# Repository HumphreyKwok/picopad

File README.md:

# picopad
A Cherry-mx numpad for fun

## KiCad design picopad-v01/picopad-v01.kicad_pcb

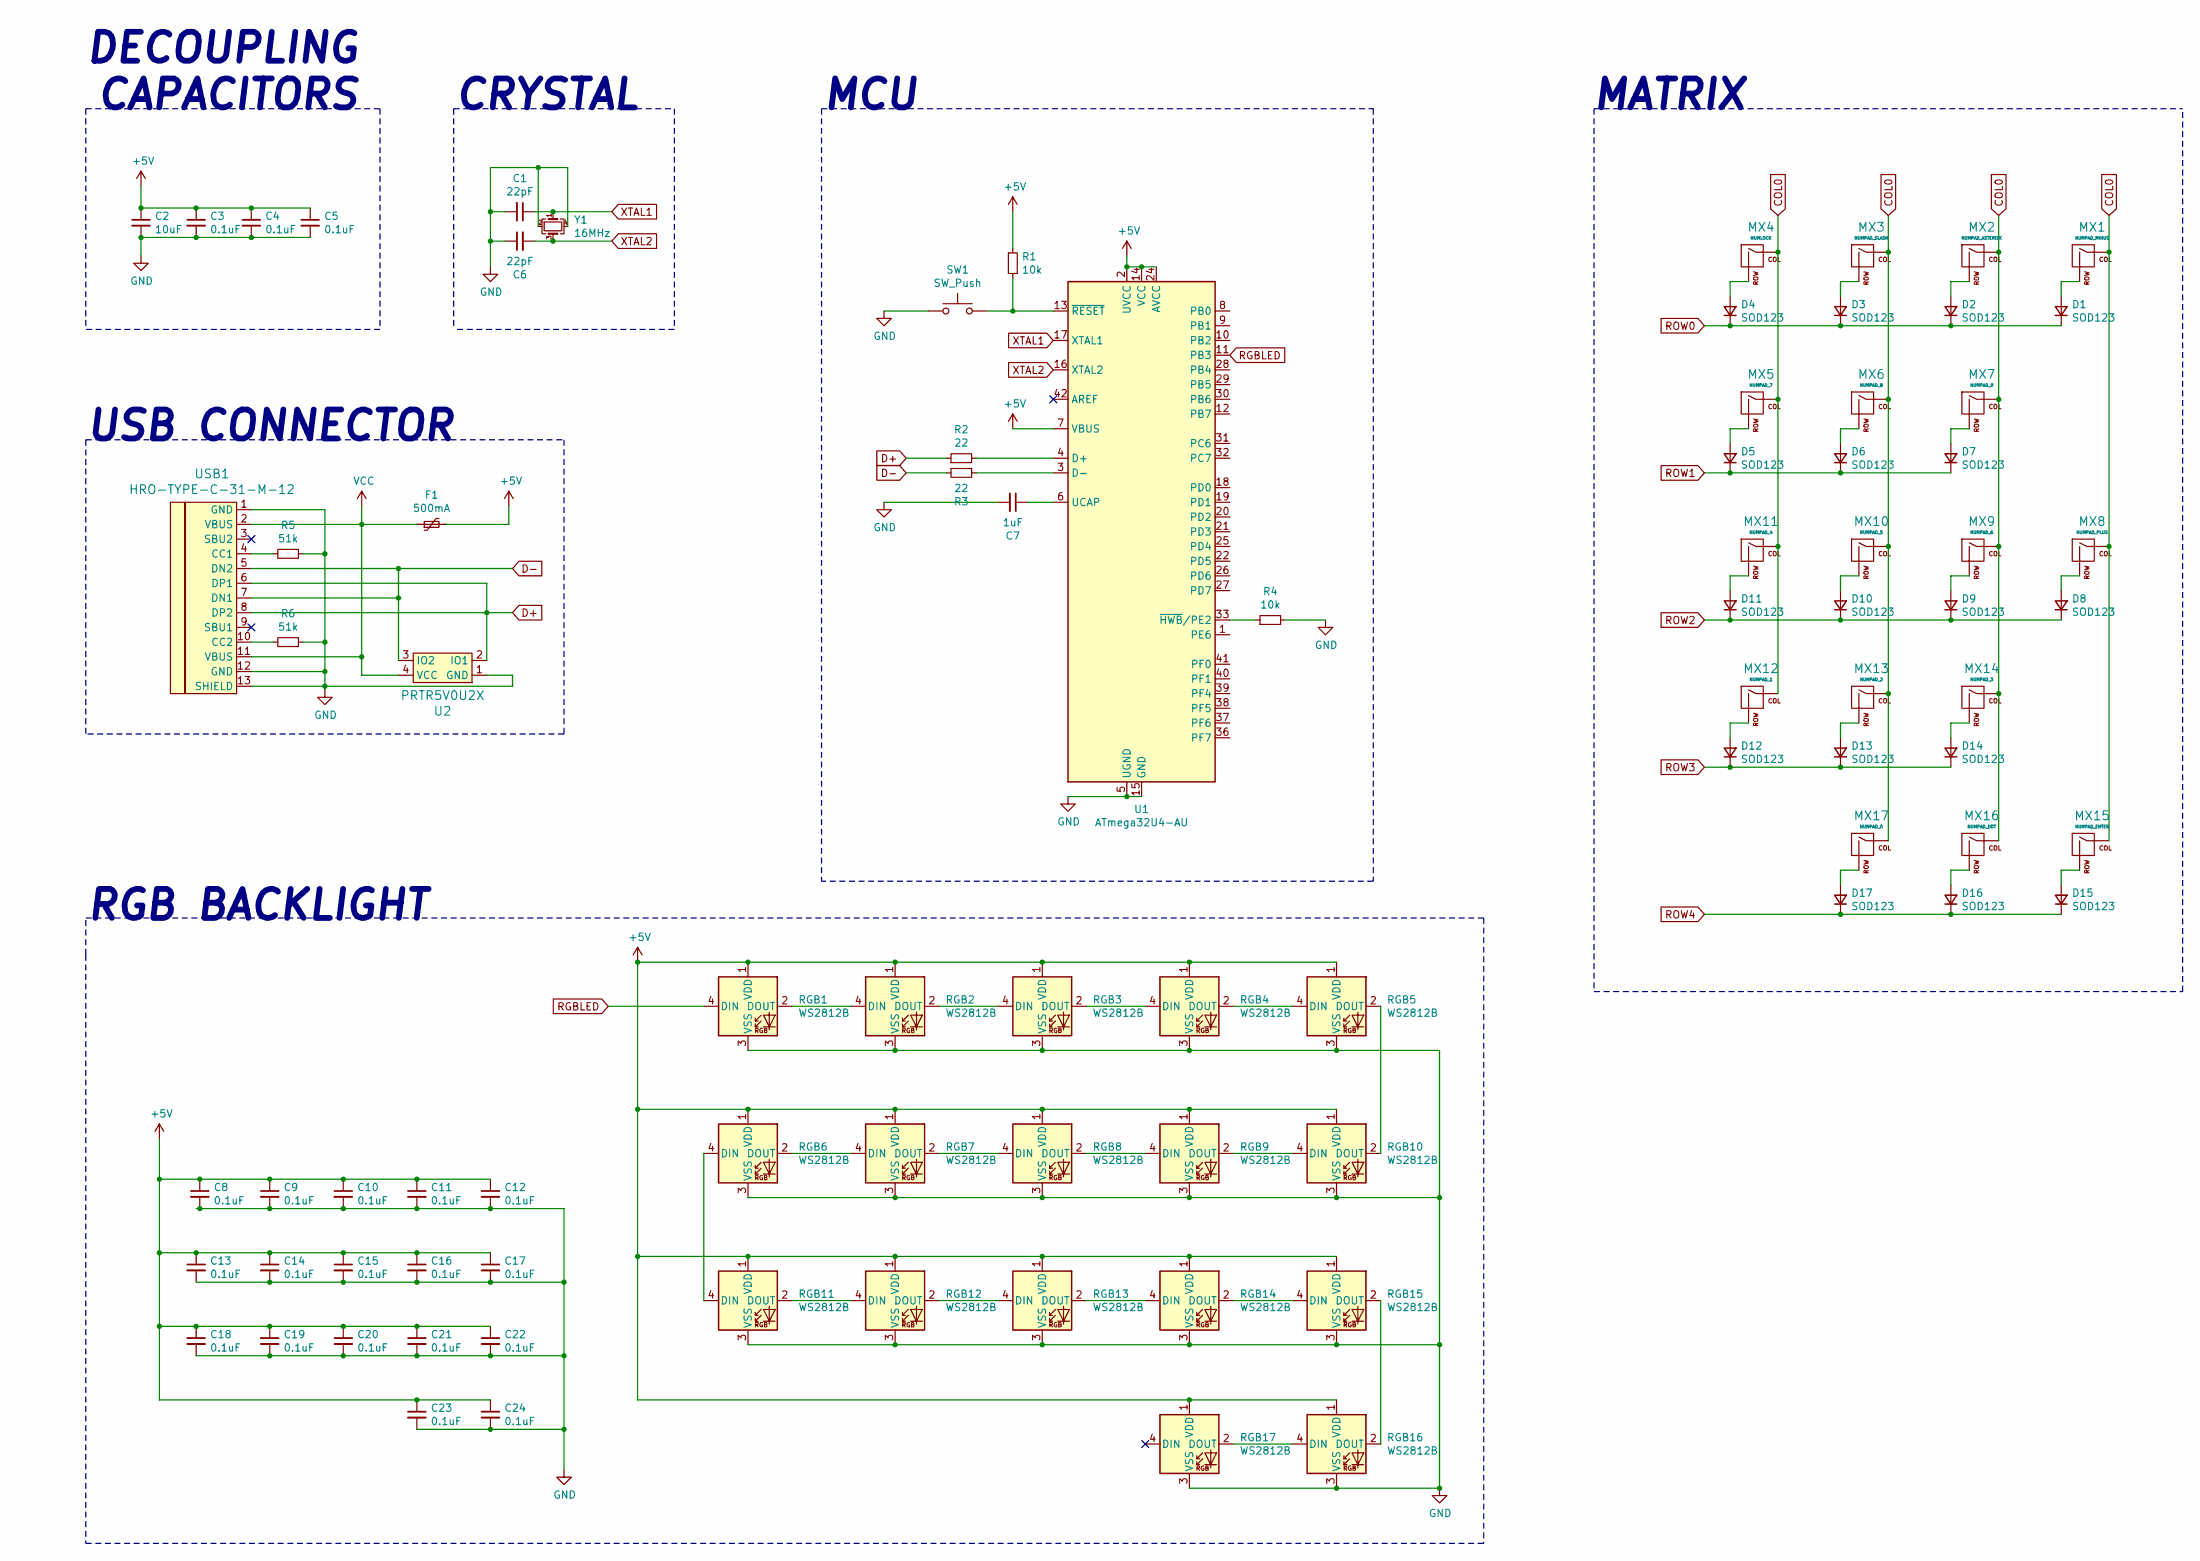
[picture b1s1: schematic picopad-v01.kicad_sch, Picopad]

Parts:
C1, C6: 22pF; C_0805_2012Metric
C2: 10uF; C_0805_2012Metric
C3, C4, C5: 0.1uF; C_0805_2012Metric
C7: 1uF; C_0805_2012Metric
C8, C9, C10, C11, C12, C13, C14, C15, C16, C17, C18, C19, C20, C21, C22, C23, C24: 0.1uF; C_0603_1608Metric
D1, D2, D3, D4, D5, D6, D7, D8, D9, D10, D11, D12, D13, D14, D15, D16, D17: SOD123; D_SOD-123
F1: 500mA; Fuse_1206_3216Metric
MX1: NUMPAD_MINUS; MXOnly-1U-Hotswap
MX2: NUMPAD_ASTERISK; MXOnly-1U-Hotswap
MX3: NUMPAD_SLASH; MXOnly-1U-Hotswap
MX4: NUMLOCK; MXOnly-1U-Hotswap
MX5: NUMPAD_7; MXOnly-1U-Hotswap
MX6: NUMPAD_8; MXOnly-1U-Hotswap
MX7: NUMPAD_9; MXOnly-1U-Hotswap
MX8: NUMPAD_PLUS; MXOnly-2U-Hotswap-Vertical
MX9: NUMPAD_6; MXOnly-1U-Hotswap
MX10: NUMPAD_5; MXOnly-1U-Hotswap
MX11: NUMPAD_4; MXOnly-1U-Hotswap
MX12: NUMPAD_1; MXOnly-1U-Hotswap
MX13: NUMPAD_2; MXOnly-1U-Hotswap
MX14: NUMPAD_3; MXOnly-1U-Hotswap
MX15: NUMPAD_ENTER; MXOnly-2U-Hotswap-Vertical
MX16: NUMPAD_DOT; MXOnly-1U-Hotswap
MX17: NUMPAD_0; MXOnly-2U-Hotswap
R1, R4: 10k; R_0805_2012Metric
R2, R3: 22; R_0805_2012Metric
R5, R6: 51k; R_0805_2012Metric
RGB1, RGB2, RGB3, RGB4, RGB5, RGB6, RGB7, RGB8, RGB9, RGB10, RGB11, RGB12, RGB13, RGB14, RGB15, RGB16, RGB17: WS2812B; WS2812B-3528
SW1: SW_Push; SKQG-1155865
U1: ATmega32U4-AU; TQFP-44_10x10mm_P0.8mm
U2: PRTR5V0U2X; SOT143B
USB1: HRO-TYPE-C-31-M-12
Y1: 16MHz; Crystal_SMD_3225-4Pin_3.2x2.5mm

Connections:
+5V: C2.1, C3.1, C4.1, C5.1, C8.1, C9.1, C10.1, C11.1, C12.1, C13.1, C14.1, C15.1, C16.1, C17.1, C18.1, C19.1, C20.1, C21.1, C22.1, C23.1, C24.1, F1.2, R1.1, RGB1.1 (VDD), RGB2.1 (VDD), RGB3.1 (VDD), RGB4.1 (VDD), RGB5.1 (VDD), RGB6.1 (VDD), RGB7.1 (VDD), RGB8.1 (VDD), RGB9.1 (VDD), RGB10.1 (VDD), RGB11.1 (VDD), RGB12.1 (VDD), RGB13.1 (VDD), RGB14.1 (VDD), RGB15.1 (VDD), RGB16.1 (VDD), RGB17.1 (VDD), U1.2 (UVCC), U1.7 (VBUS), U1.14 (VCC), U1.24 (AVCC), U1.34 (VCC), U1.44 (AVCC)
COL0: MX1.1 (COL), MX2.1 (COL), MX3.1 (COL), MX4.1 (COL), MX5.1 (COL), MX6.1 (COL), MX7.1 (COL), MX8.1 (COL), MX9.1 (COL), MX10.1 (COL), MX11.1 (COL), MX12.1 (COL), MX13.1 (COL), MX14.1 (COL), MX15.1 (COL), MX16.1 (COL), MX17.1 (COL)
D+: R2.1, U2.2 (IO1), USB1.6 (DP1), USB1.8 (DP2)
D-: R3.2, U2.3 (IO2), USB1.5 (DN2), USB1.7 (DN1)
unnamed: C7.1, U1.6 (UCAP)
unnamed: D1.2 (A), MX1.2 (ROW)
unnamed: D2.2 (A), MX2.2 (ROW)
unnamed: D3.2 (A), MX3.2 (ROW)
unnamed: D4.2 (A), MX4.2 (ROW)
unnamed: D5.2 (A), MX5.2 (ROW)
unnamed: D6.2 (A), MX6.2 (ROW)
unnamed: D7.2 (A), MX7.2 (ROW)
unnamed: D11.2 (A), MX11.2 (ROW)
unnamed: D10.2 (A), MX10.2 (ROW)
unnamed: D9.2 (A), MX9.2 (ROW)
unnamed: D8.2 (A), MX8.2 (ROW)
unnamed: D12.2 (A), MX12.2 (ROW)
unnamed: D13.2 (A), MX13.2 (ROW)
unnamed: D14.2 (A), MX14.2 (ROW)
unnamed: D17.2 (A), MX17.2 (ROW)
unnamed: D16.2 (A), MX16.2 (ROW)
unnamed: D15.2 (A), MX15.2 (ROW)
unnamed: R1.2, SW1.2, U1.13 (~RESET)
unnamed: R2.2, U1.4 (D+)
unnamed: R3.1, U1.3 (D-)
unnamed: R4.1, U1.33 (~HWB~/PE2)
unnamed: R5.2, USB1.4 (CC1)
unnamed: R6.2, USB1.10 (CC2)
unnamed: RGB1.2 (DOUT), RGB2.4 (DIN)
unnamed: RGB2.2 (DOUT), RGB3.4 (DIN)
unnamed: RGB3.2 (DOUT), RGB4.4 (DIN)
unnamed: RGB4.2 (DOUT), RGB5.4 (DIN)
unnamed: RGB6.2 (DOUT), RGB7.4 (DIN)
unnamed: RGB7.2 (DOUT), RGB8.4 (DIN)
unnamed: RGB8.2 (DOUT), RGB9.4 (DIN)
unnamed: RGB5.2 (DOUT), RGB10.2 (DOUT)
unnamed: RGB9.2 (DOUT), RGB10.4 (DIN)
unnamed: RGB11.2 (DOUT), RGB12.4 (DIN)
unnamed: RGB6.4 (DIN), RGB11.4 (DIN)
unnamed: RGB12.2 (DOUT), RGB13.4 (DIN)
unnamed: RGB13.2 (DOUT), RGB14.4 (DIN)
unnamed: RGB14.2 (DOUT), RGB15.4 (DIN)
unnamed: RGB15.2 (DOUT), RGB16.2 (DOUT)
unnamed: RGB16.4 (DIN), RGB17.2 (DOUT)
RGBLED: RGB1.4 (DIN), U1.11 (PB3)
ROW0: D1.1 (K), D2.1 (K), D3.1 (K), D4.1 (K)
ROW1: D5.1 (K), D6.1 (K), D7.1 (K)
ROW2: D8.1 (K), D9.1 (K), D10.1 (K), D11.1 (K)
ROW3: D12.1 (K), D13.1 (K), D14.1 (K)
ROW4: D15.1 (K), D16.1 (K), D17.1 (K)
VCC: F1.1, U2.4 (VCC), USB1.2 (VBUS), USB1.11 (VBUS)
XTAL1: C1.1, U1.17 (XTAL1), Y1.1
XTAL2: C6.2, U1.16 (XTAL2), Y1.3

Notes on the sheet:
DECOUPLING CAPACITORS
RGB BACKLIGHT
USB CONNECTOR
CRYSTAL
MCU
MATRIX

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
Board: 2 copper layers, 87 parts (70 on the bottom side), 54 nets, no tracks yet.

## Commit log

2020-06-17 Add libraries
2020-06-17 Create KiCAD files
2020-06-18 Create the MCU and USB connector shcematic
2020-06-18 Complete the schematic
2020-06-18 Create a footprint of WS2812B-3528
2020-06-18 Add RGB backlight support
2020-06-19 Modified some footprints for SMD leds
2020-06-19 Complete the footprint assignment
2020-06-19 Place the footprints on the PCB
2020-06-19 Fix some positioning issue
2020-06-19 Fix some positioning isuue for vertical 2u footprints
2020-06-19 Fix some footprint
2020-06-20 Add Picopad v02 which support side glow keycaps

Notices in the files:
picopad-v01/picopad-v01.kicad_pcb:
License: MIT
